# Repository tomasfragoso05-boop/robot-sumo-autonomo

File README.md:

# Autonomous Sumo Robot (ATmega328P)

An autonomous mini-sumo robot built from scratch: a custom PCB designed in KiCad, a bare-metal C firmware for the ATmega328P (no Arduino libraries), and a hand-built aluminium chassis with a front ramp to push opponents out of the ring.

<p align="center">
  
  &nbsp;&nbsp;
  
</p>

Full match video: [`media/match.mp4`](media/match.mp4)

## How it works

Once powered, the robot waits 1 s and then runs a priority-based control loop with no human input:

1. **Front edge detected** (front line sensors see the black border): stop, reverse for 300 ms, then spin about 840 ms to face the arena again.
2. **Rear edge detected**: drive forward for 600 ms to get away from the border.
3. **Opponent within 20 cm** (ultrasonic sensor): charge at full attack speed. During the charge the robot keeps checking the front edge sensors, so it doesn't follow the opponent out of the ring.
4. **Nothing detected**: move forward slowly to search.

A status LED blinks at 1 Hz while the robot is running.

## Hardware

| Function | Component |
|---|---|
| Microcontroller | ATmega328P (DIP-28), 16 MHz crystal |
| Motor drivers | 2 × BTS7960 H-bridge |
| Motors | 2 × DC gear motors, differential drive |
| Opponent detection | HC-SR04 ultrasonic sensor |
| Edge detection | 4 × TCRT5000 reflective IR sensors (front left/right, rear left/right) |
| Power | 3S LiPo 2200 mAh (11.1 V) + step-down converter to 5 V |
| Chassis | Bent aluminium sheet with front ramp |

The PCB (2 layers, SMD passives) carries the microcontroller, the connectors for the drivers and sensors, and the regulator. KiCad 9 sources are in [`hardware/kicad/`](hardware/kicad).

### Pin mapping

| Signal | Pin | Peripheral |
|---|---|---|
| Left motor forward / reverse | PD6 / PD5 | Timer0 PWM (OC0A / OC0B) |
| Right motor forward / reverse | PD3 / PB2 | Timer2 PWM (OC2B) / Timer1 PWM (OC1B) |
| Line sensors (rear L, front L, front R, rear R) | PC0, PC1, PC2, PC3 | ADC0 to ADC3 |
| Ultrasonic trigger / echo | PB0 / PD2 | GPIO, pulse width measured in software |
| Status LED | PB1 | GPIO |

## Firmware

[`firmware/main.c`](firmware/main.c) is written directly against the AVR registers:

- **PWM:** three hardware timers (Timer0, Timer1, Timer2) in Fast PWM mode drive the four motor-driver inputs, which gives independent speed and direction control for each wheel.
- **ADC:** the reflective sensors are read with AV<sub>CC</sub> reference and a /64 prescaler, and compared against a threshold (`LIMITE_PRETO`) to detect the black border.
- **Ultrasonic ranging:** a 12 µs trigger pulse, then the echo pulse is timed in software with timeouts, so a missing echo can't hang the loop.
- **Tuning:** speeds, the detection distance and the edge threshold are all `#define` constants at the top of the file.

### Build and flash

```bash
avr-gcc -mmcu=atmega328p -Os -DF_CPU=16000000UL -o sumo.elf firmware/main.c
avr-objcopy -O ihex sumo.elf sumo.hex
avrdude -c usbasp -p m328p -U flash:w:sumo.hex
```

Atmel/Microchip Studio also works: create a GCC C project for the ATmega328P and add `main.c`.

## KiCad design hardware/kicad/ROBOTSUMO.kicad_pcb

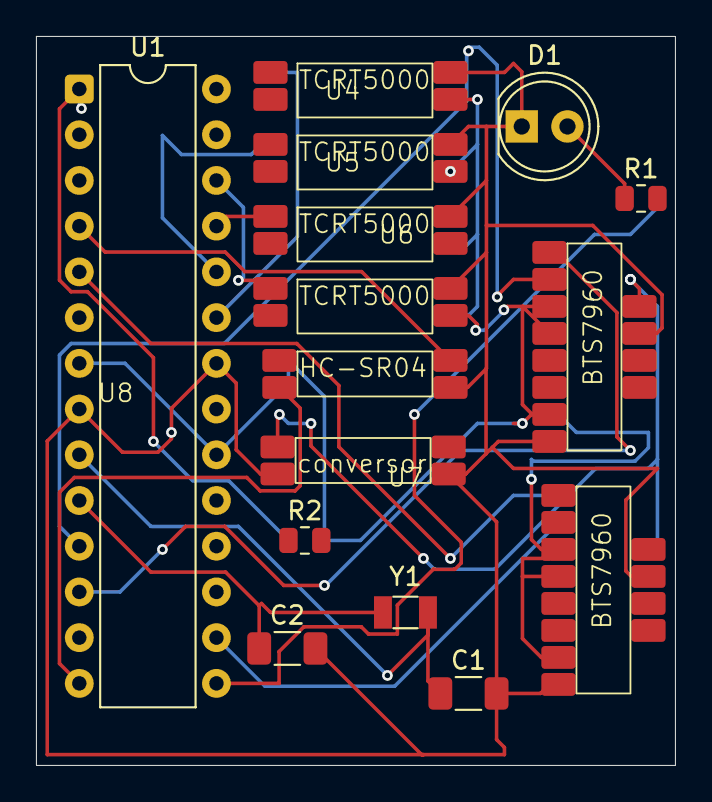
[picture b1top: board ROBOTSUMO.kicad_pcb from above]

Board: 2 copper layers, 35.5 x 40.5 mm, 15 parts (0 on the bottom side), 18 nets.

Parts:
C1, C2: C; C_1206_3216Metric_Pad1.33x1.80mm_HandSolder
D1: LED; LED_D5.0mm
HC-SR04: HC-SR04
R1: 330; R_0805_2012Metric
R2: 10k; R_0805_2012Metric
U1: ATmega328P-P; DIP-28_W7.62mm
U2, U3, U4, U5: TCRT5000
U6, U7: BTS7960
U8: Conversor; conversor
Y1: Crystal; Crystal_SMD_3215-2Pin_3.2x1.5mm

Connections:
/BAT: U6.9 (B+), U7.9 (B+), U8.1 (VIN+)
/VCC: HC-SR04.1 (VCC), R2.2, U1.7 (VCC), U1.20 (AVCC), U2.4 (VCC), U3.4 (VCC), U4.4 (VCC), U5.4 (VCC), U6.3 (L_EN), U6.4 (R_EN), U6.7 (VCC), U7.3 (L_EN), U7.4 (R_EN), U7.7 (VCC), U8.3 (VOUT+)
GND: C1.2, C2.2, D1.1 (K), HC-SR04.4 (GND), U1.8 (GND), U1.22 (GND), U2.3 (GND), U3.3 (GND), U4.3 (GND), U5.3 (GND), U6.8 (GND), U6.10 (B-), U7.8 (GND), U7.10 (B-), U8.2 (VIN-), U8.4 (VOUT-)
unnamed: D1.2 (A), R1.1
unnamed: HC-SR04.3 (ECHO), U1.4 (PD2)
unnamed: HC-SR04.2 (TRIG), U1.14 (PB0)
unnamed: R1.2, U1.15 (PB1)
unnamed: U1.16 (PB2), U7.2 (RPWM)
unnamed: U1.23 (PC0), U2.1 (A0)
unnamed: U1.24 (PC1), U3.1 (A0)
unnamed: U1.25 (PC2), U4.1 (A0)
unnamed: U1.26 (PC3), U5.1 (A0)
unnamed: U1.5 (PD3), U7.1 (LPWM)
unnamed: U1.11 (PD5), U6.2 (RPWM)
unnamed: U1.12 (PD6), U6.1 (LPWM)
unnamed: C1.1, U1.9 (XTAL1/PB6), Y1.1
unnamed: C2.1, U1.10 (XTAL2/PB7), Y1.2
unnamed: R2.1, U1.1 (~RESET/PC6)

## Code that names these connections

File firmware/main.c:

#define F_CPU 16000000UL
#include <avr/io.h>
#include <util/delay.h>
#include <stdint.h>

// --- MAPEAMENTO DE PINOS CONFIRMADO ---
#define PIN_FRENTE_ESQ  1  // PC1 (A1)
#define PIN_TRAS_ESQ    0  // PC0 (A0)
#define PIN_FRENTE_DIR  2  // PC2 (A2)
#define PIN_TRAS_DIR    3  // PC3 (A3)

#define VEL_LENTA       90
#define VEL_ATAQUE      150
#define VEL_FUGA        150
#define DIST_DETECAO    20
#define LIMITE_PRETO    450  // Acima disto é a borda (Preta)

uint32_t milis_total = 0;

// --- MOVIMENTOS ---
void parar() { OCR0A = 0; OCR0B = 0; OCR2B = 0; OCR1B = 0; }
void andar_frente(uint8_t vel) { OCR0A = vel; OCR0B = 0; OCR2B = vel; OCR1B = 0; }
void andar_tras(uint8_t vel) { OCR0A = 0; OCR0B = vel; OCR2B = 0; OCR1B = vel; }
void rodar_esquerda(uint8_t vel) { OCR0A = 0; OCR0B = vel; OCR2B = vel; OCR1B = 0; }

void gerir_led(uint16_t incremento_ms) {
	milis_total += incremento_ms;
	if ((milis_total % 1000) < 500) PORTB |= (1 << PB1);
	else PORTB &= ~(1 << PB1);
}

uint16_t ler_linha(uint8_t canal) {
	ADMUX = (1 << REFS0) | (canal & 0x07);
	_delay_us(50);
	ADCSRA |= (1 << ADSC);
	while (ADCSRA & (1 << ADSC));
	return ADC;
}

uint16_t get_distancia() {
	PORTB |= (1 << PB0);
	_delay_us(12);
	PORTB &= ~(1 << PB0);
	uint32_t timeout = 35000;
	while (!(PIND & (1 << PD2)) && timeout--) ;
	if (timeout == 0) return 999;
	uint32_t count = 0;
	while ((PIND & (1 << PD2)) && count < 30000) {
		_delay_us(1);
		count++;
	}
	return count / 58;
}

int main(void) {
	DDRD |= (1 << PD5) | (1 << PD6) | (1 << PD3);
	DDRB |= (1 << PB2) | (1 << PB1) | (1 << PB0);
	DDRD &= ~(1 << PD2);

	TCCR0A = (1 << COM0A1) | (1 << COM0B1) | (1 << WGM00) | (1 << WGM01);
	TCCR0B = (1 << CS01);
	TCCR2A = (1 << COM2B1) | (1 << WGM20) | (1 << WGM21);
	TCCR2B = (1 << CS21);
	TCCR1A = (1 << COM1B1) | (1 << WGM10);
	TCCR1B = (1 << WGM12) | (1 << CS11);
	ADCSRA = (1 << ADEN) | (1 << ADPS2) | (1 << ADPS1);

	parar();
	_delay_ms(1000);

	while (1) {
		// --- 1. SENSORES DA FRENTE (Borda Preta detetada) ---
		if (ler_linha(PIN_FRENTE_ESQ) > LIMITE_PRETO || ler_linha(PIN_FRENTE_DIR) > LIMITE_PRETO) {
			parar(); _delay_ms(50);
			andar_tras(VEL_FUGA);
			for(int i=0; i<15; i++) { _delay_ms(20); gerir_led(20); }
			rodar_esquerda(VEL_FUGA);
			for(int i=0; i<42; i++) { _delay_ms(20); gerir_led(20); }
			continue;
		}

		// --- 2. SENSORES DE TRÁS (Borda Preta detetada) ---
		if (ler_linha(PIN_TRAS_ESQ) > LIMITE_PRETO || ler_linha(PIN_TRAS_DIR) > LIMITE_PRETO) {
			andar_frente(VEL_FUGA);
			for(int i=0; i<30; i++) { _delay_ms(20); gerir_led(20); }
			continue;
		}

		// --- 3. COMBATE ---
		uint16_t dist = get_distancia();

		if (dist > 0 && dist < DIST_DETECAO) {
			andar_frente(VEL_ATAQUE);
			for(int i = 0; i < 5; i++) {
				_delay_ms(20);
				gerir_led(20);
				// Proteção: verifica se atingiu a borda preta durante o ataque
				if (ler_linha(PIN_FRENTE_ESQ) > LIMITE_PRETO || ler_linha(PIN_FRENTE_DIR) > LIMITE_PRETO) break;
			}
			} else {
			andar_frente(VEL_LENTA);
			_delay_ms(50);
			gerir_led(50);
		}
	}
}
